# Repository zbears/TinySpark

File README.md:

## Tiny Spark Programming Shield

An arduino shield designed to allow programming of ATTiny microcontrollers

## Supported Devices

This shield supports the following ATTiny Microcontrollers: 
* ATTiny 85, 45, 25, 15, 13, 84, 44, 24, 2313, and 4313

## Instructions For Use

A detailed writeup of the project and instructions for its use can be found [here](http://www.zacharybears.com/works/tinyspark-programming-shield/).

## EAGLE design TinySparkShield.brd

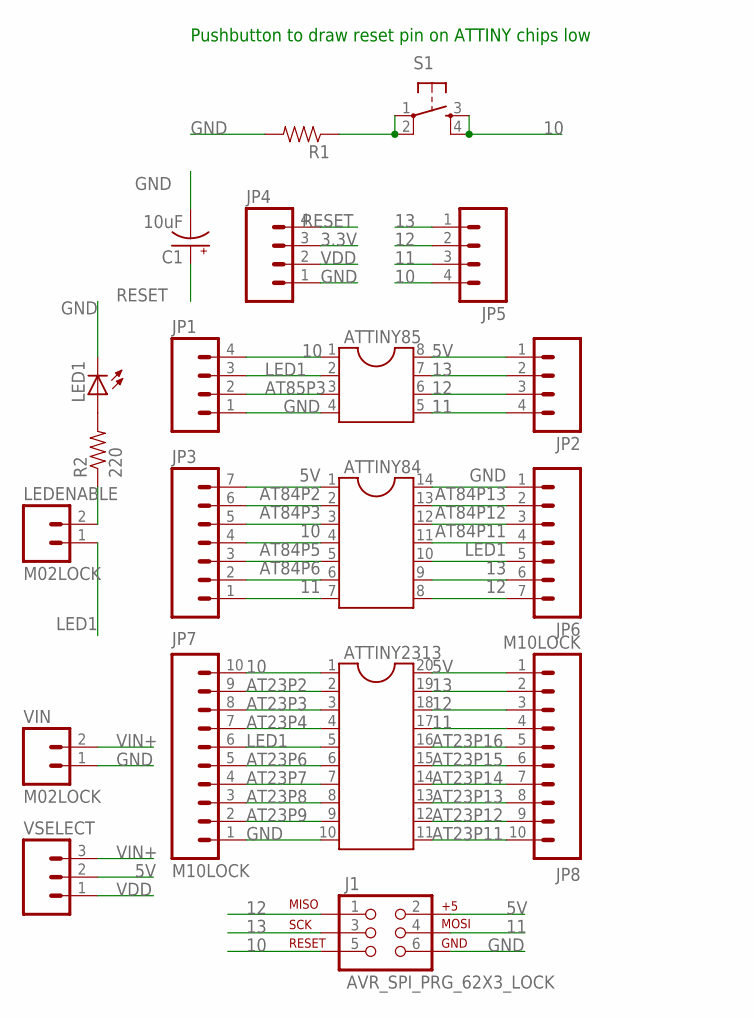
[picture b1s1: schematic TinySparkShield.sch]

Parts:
ATTINY84: DIL14
ATTINY85: DIL8; DIL08
ATTINY2313: DIL20
C1: 10uF; CPOL-RADIAL-100UF-25V
J1: AVR_SPI_PRG_62X3_LOCK; 2X3_LOCK
JP1, JP2, JP4, JP5: M04LOCK; 1X04_LOCK
JP3, JP6: M07LOCK; 1X07_LOCK
JP7, JP8: M10LOCK; 1X10_LOCK
LED1: LED3MM
LEDENABLE: M02LOCK; 1X02_LOCK
R1: RESISTORAXIAL-0.3; AXIAL-0.3
R2: 220; AXIAL-0.3
S1: TAC_SWITCHPTH; TACTILE-PTH
VIN: M02LOCK; 1X02_LOCK
VSELECT: M03LOCK; 1X03_LOCK

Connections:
3.3V: JP4.3
5V: ATTINY84.1, ATTINY85.8, ATTINY2313.20, J1.2, JP2.1, JP3.7, JP8.1, VSELECT.2
10: ATTINY84.4, ATTINY85.1, ATTINY2313.1, J1.5, JP1.4, JP3.4, JP5.4, JP7.10, S1.3, S1.4
11: ATTINY84.7, ATTINY85.5, ATTINY2313.17, J1.4, JP2.4, JP3.1, JP5.3, JP8.4
12: ATTINY84.8, ATTINY85.6, ATTINY2313.18, J1.1, JP2.3, JP5.2, JP6.7, JP8.3
13: ATTINY84.9, ATTINY85.7, ATTINY2313.19, J1.3, JP2.2, JP5.1, JP6.6, JP8.2
AT23P2: ATTINY2313.2, JP7.9
AT23P3: ATTINY2313.3, JP7.8
AT23P4: ATTINY2313.4, JP7.7
AT23P6: ATTINY2313.6, JP7.5
AT23P7: ATTINY2313.7, JP7.4
AT23P8: ATTINY2313.8, JP7.3
AT23P9: ATTINY2313.9, JP7.2
AT23P11: ATTINY2313.11, JP8.10
AT23P12: ATTINY2313.12, JP8.9
AT23P13: ATTINY2313.13, JP8.8
AT23P14: ATTINY2313.14, JP8.7
AT23P15: ATTINY2313.15, JP8.6
AT23P16: ATTINY2313.16, JP8.5
AT84P2: ATTINY84.2, JP3.6
AT84P3: ATTINY84.3, JP3.5
AT84P5: ATTINY84.5, JP3.3
AT84P6: ATTINY84.6, JP3.2
AT84P11: ATTINY84.11, JP6.4
AT84P12: ATTINY84.12, JP6.3
AT84P13: ATTINY84.13, JP6.2
AT85P3: ATTINY85.3, JP1.2
GND: ATTINY84.14, ATTINY85.4, ATTINY2313.10, C1.2 (-), J1.6, JP1.1, JP4.1, JP6.1, JP7.1, LED1.K (C), R1.P$2 (2), VIN.1
LED1: ATTINY84.10, ATTINY85.2, ATTINY2313.5, JP1.3, JP6.5, JP7.6, LEDENABLE.1
unnamed: LED1.A, R2.P$2 (2)
unnamed: LEDENABLE.2, R2.P$1 (1)
unnamed: R1.P$1 (1), S1.1, S1.2
RESET: C1.1 (+), JP4.4
VDD: JP4.2, VSELECT.1
VIN+: VIN.2, VSELECT.3

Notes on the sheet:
Pushbutton to draw reset pin on ATTINY chips low

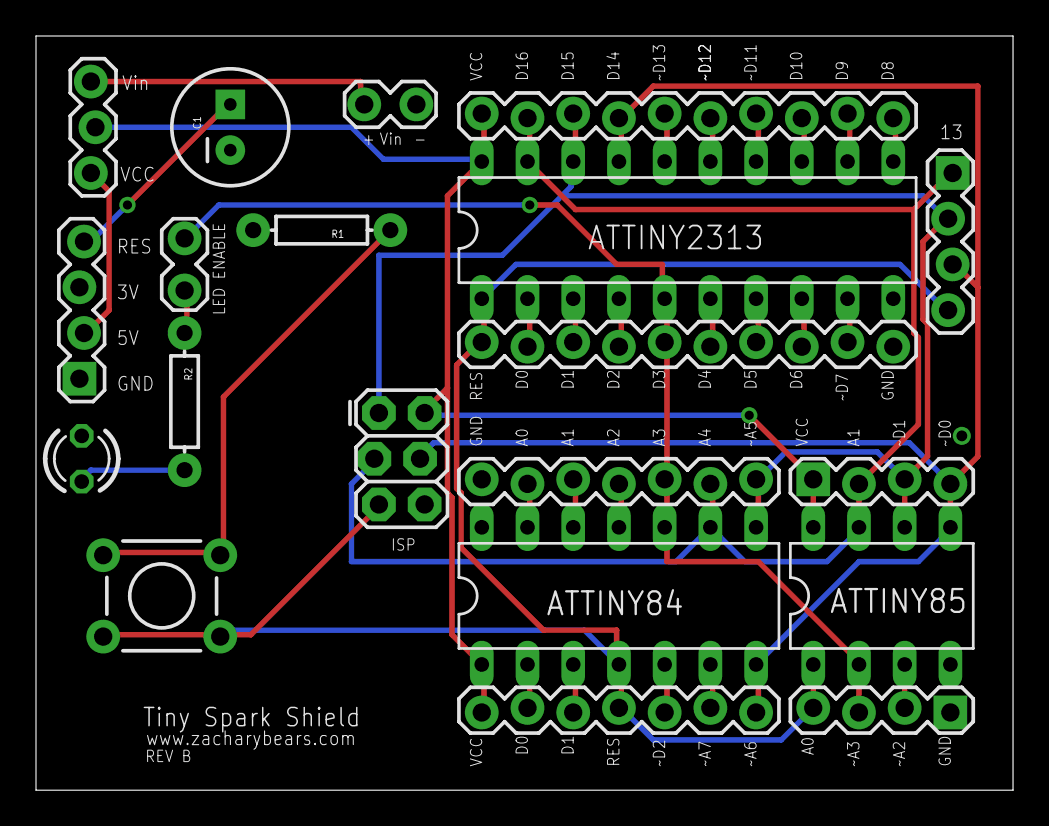
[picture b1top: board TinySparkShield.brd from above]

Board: 2 copper layers, 54.3 x 41.9 mm, 20 parts (0 on the bottom side), 34 nets.

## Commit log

2014-03-13 Initial Commit
    Added Eagle board files
2014-03-13 Initial edits to README

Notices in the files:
parts and their libraries:
SparkFun-Connectors: Licensing: CC v3.0 Share-Alike You are welcome to use this library for commercial purposes.
